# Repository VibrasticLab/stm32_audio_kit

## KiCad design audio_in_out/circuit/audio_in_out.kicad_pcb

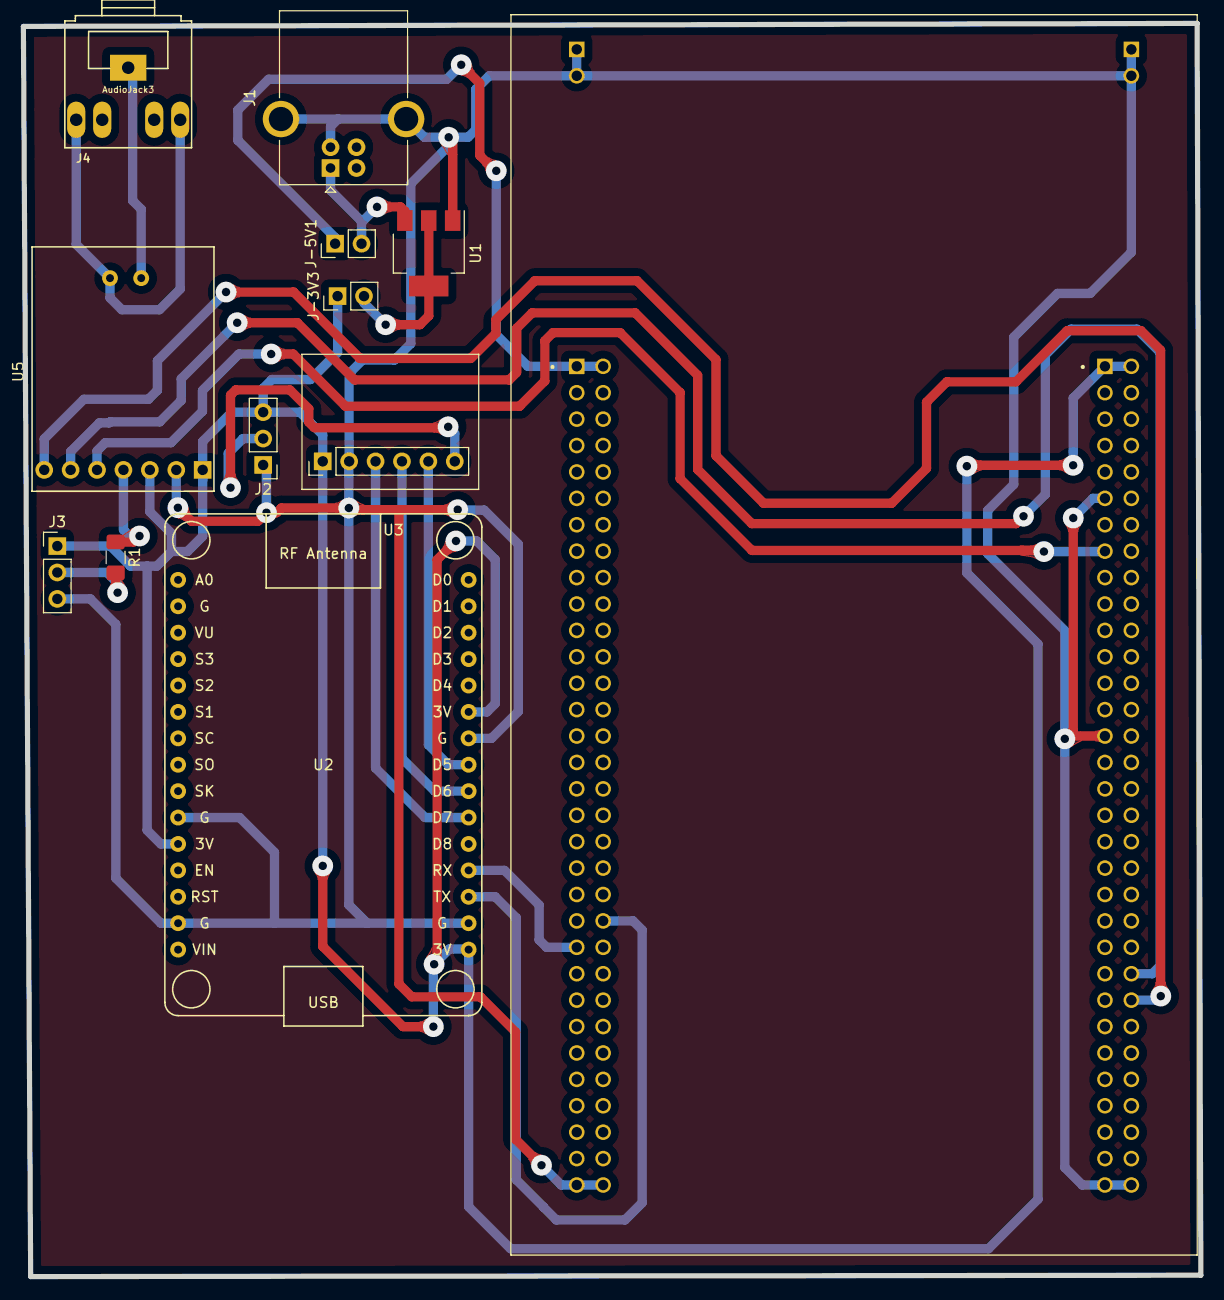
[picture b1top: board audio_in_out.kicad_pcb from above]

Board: 2 copper layers, 113.2 x 120.5 mm, 12 parts (0 on the bottom side), 18 nets.

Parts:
J1: USB_B; USB_B_OST_USB-B1HSxx_Horizontal
J2, J3: Conn_01x03_Male; PinHeader_1x03_P2.54mm_Vertical
J4: AudioJack3; Tayda_3.5mm_stereo_TRS_jack_A-853
J-3V3, J-5V1: Conn_01x02_Male; PinHeader_1x02_P2.54mm_Vertical
R1: 100k; R_1206_3216Metric_Pad1.42x1.75mm_HandSolder
U1: AMS1117-3.3; SOT-223-3_TabPin2
U2: NodeMCU1.0(ESP-12E); NodeMCU1.0(12-E)
U3: SPH0645; sph0645
U4: STM32F429I-DISC1
U5: MAX98357_DAC; dacmax98357

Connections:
+3V3: J2.3, J3.1, J-3V3.1, U2.11, U2.16, U2.25, U3.1, U4.P2_1, U4.P2_2, U5.1, U5.3
+5V: J-5V1.1, U4.P1_1, U4.P1_2
/BCLK: U2.21, U3.3
/DAC_BCLK: U4.P2_48, U5.6
/DAC_DIN: U4.P2_15, U5.5
/DAC_LRC: U4.P2_50, U5.7
/DOUT: U2.22, U3.4
/LRCL: U2.23, U3.5
/RX: U2.18, U4.P1_44
/TX: U2.19, U4.P1_45
GND: J1.4, J1.5, J2.1, J3.3, U1.1, U2.10, U2.14, U2.17, U2.24, U3.2, U4.JP1_1, U4.JP1_2, U4.JP2_1, U4.JP2_2, U4.P1_63, U4.P1_64, U4.P2_11, U4.P2_29, U4.P2_63, U4.P2_64, U5.2
unnamed: J2.2, U3.6
unnamed: J3.2, R1.2
unnamed: J4.R, J4.T, U5.9
unnamed: J4.S, U5.8
unnamed: J-3V3.2, U1.2
unnamed: R1.1, U5.4
VCC: J1.1, J-5V1.2, U1.3

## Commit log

2020-10-09 initial
2020-10-09 pcb print
2020-10-09 mp3 player
